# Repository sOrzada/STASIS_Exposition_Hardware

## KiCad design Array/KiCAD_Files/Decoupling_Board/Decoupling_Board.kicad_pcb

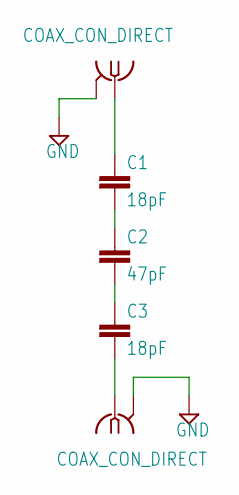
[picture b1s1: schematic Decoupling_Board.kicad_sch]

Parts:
C1, C3: 18pF; C1210
C2: 47pF; C1210
U$1, U$2: COAX_CON_DIRECT; COAX.141

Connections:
GND: U$1.P$2 (GND@1), U$2.P$2 (GND@1)
unnamed: C1.1, U$1.P$1 (1)
unnamed: C1.2, C2.1
unnamed: C2.2, C3.1
unnamed: C3.2, U$2.P$1 (1)

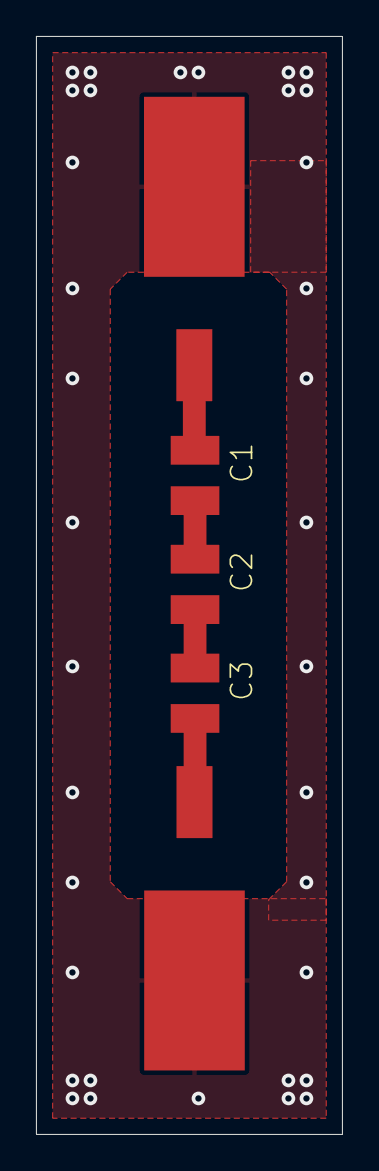
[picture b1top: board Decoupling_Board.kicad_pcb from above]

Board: 2 copper layers, 17.0 x 61.0 mm, 5 parts (0 on the bottom side), 5 nets.

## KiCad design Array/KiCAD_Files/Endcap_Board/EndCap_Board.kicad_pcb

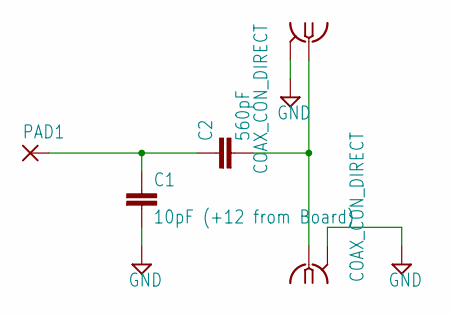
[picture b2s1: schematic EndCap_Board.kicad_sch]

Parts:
C1: 10pF (+12 from Board); C1210
C2: 560pF; C1210
PAD1: SMD5; SMD2,54-5,08
U$1, U$2: COAX_CON_DIRECT; COAX.141

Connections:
GND: C1.2, U$1.P$2 (GND@1), U$2.P$2 (GND@1)
unnamed: C1.1, C2.1, PAD1.1
unnamed: C2.2, U$1.P$1 (1), U$2.P$1 (1)

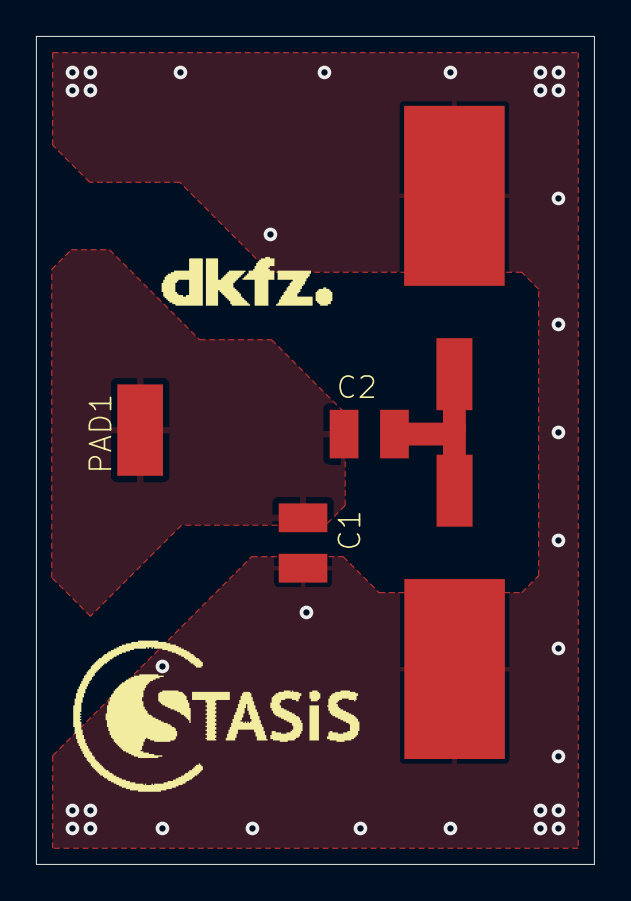
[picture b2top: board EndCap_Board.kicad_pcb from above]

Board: 2 copper layers, 31.0 x 46.0 mm, 7 parts (0 on the bottom side), 3 nets.

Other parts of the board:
U$3: LOGO_STASIS
U$4: LOGO_DKFZ

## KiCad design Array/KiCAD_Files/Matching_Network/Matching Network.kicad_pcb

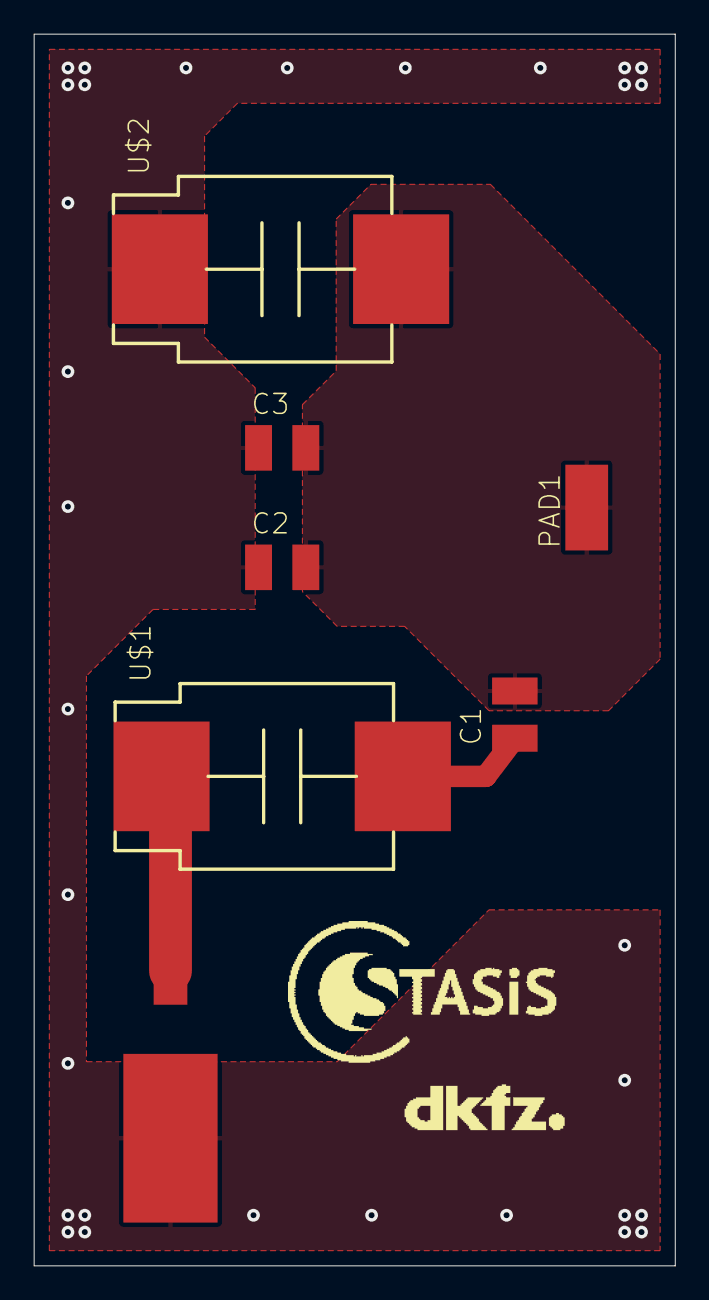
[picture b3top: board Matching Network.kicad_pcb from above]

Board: 2 copper layers, 38.0 x 73.0 mm, 9 parts (0 on the bottom side), 4 nets.

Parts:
C1, C2: 18pF; C1210_334
C3: 47pF; C1210_334
PAD1: SMD2,54-5,08_412
U$1, U$2: AJ25HV
U$3: COAX_CON_DIRECT; COAX.141
U$4: LOGO_STASIS
U$5: LOGO_DKFZ

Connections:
GND: C2.1, C3.1, U$2.P$1, U$3.P$2
unnamed: C1.1, U$1.P$2
unnamed: C1.2, C2.2, C3.2, PAD1.1, U$2.P$2
unnamed: U$1.P$1, U$3.P$1

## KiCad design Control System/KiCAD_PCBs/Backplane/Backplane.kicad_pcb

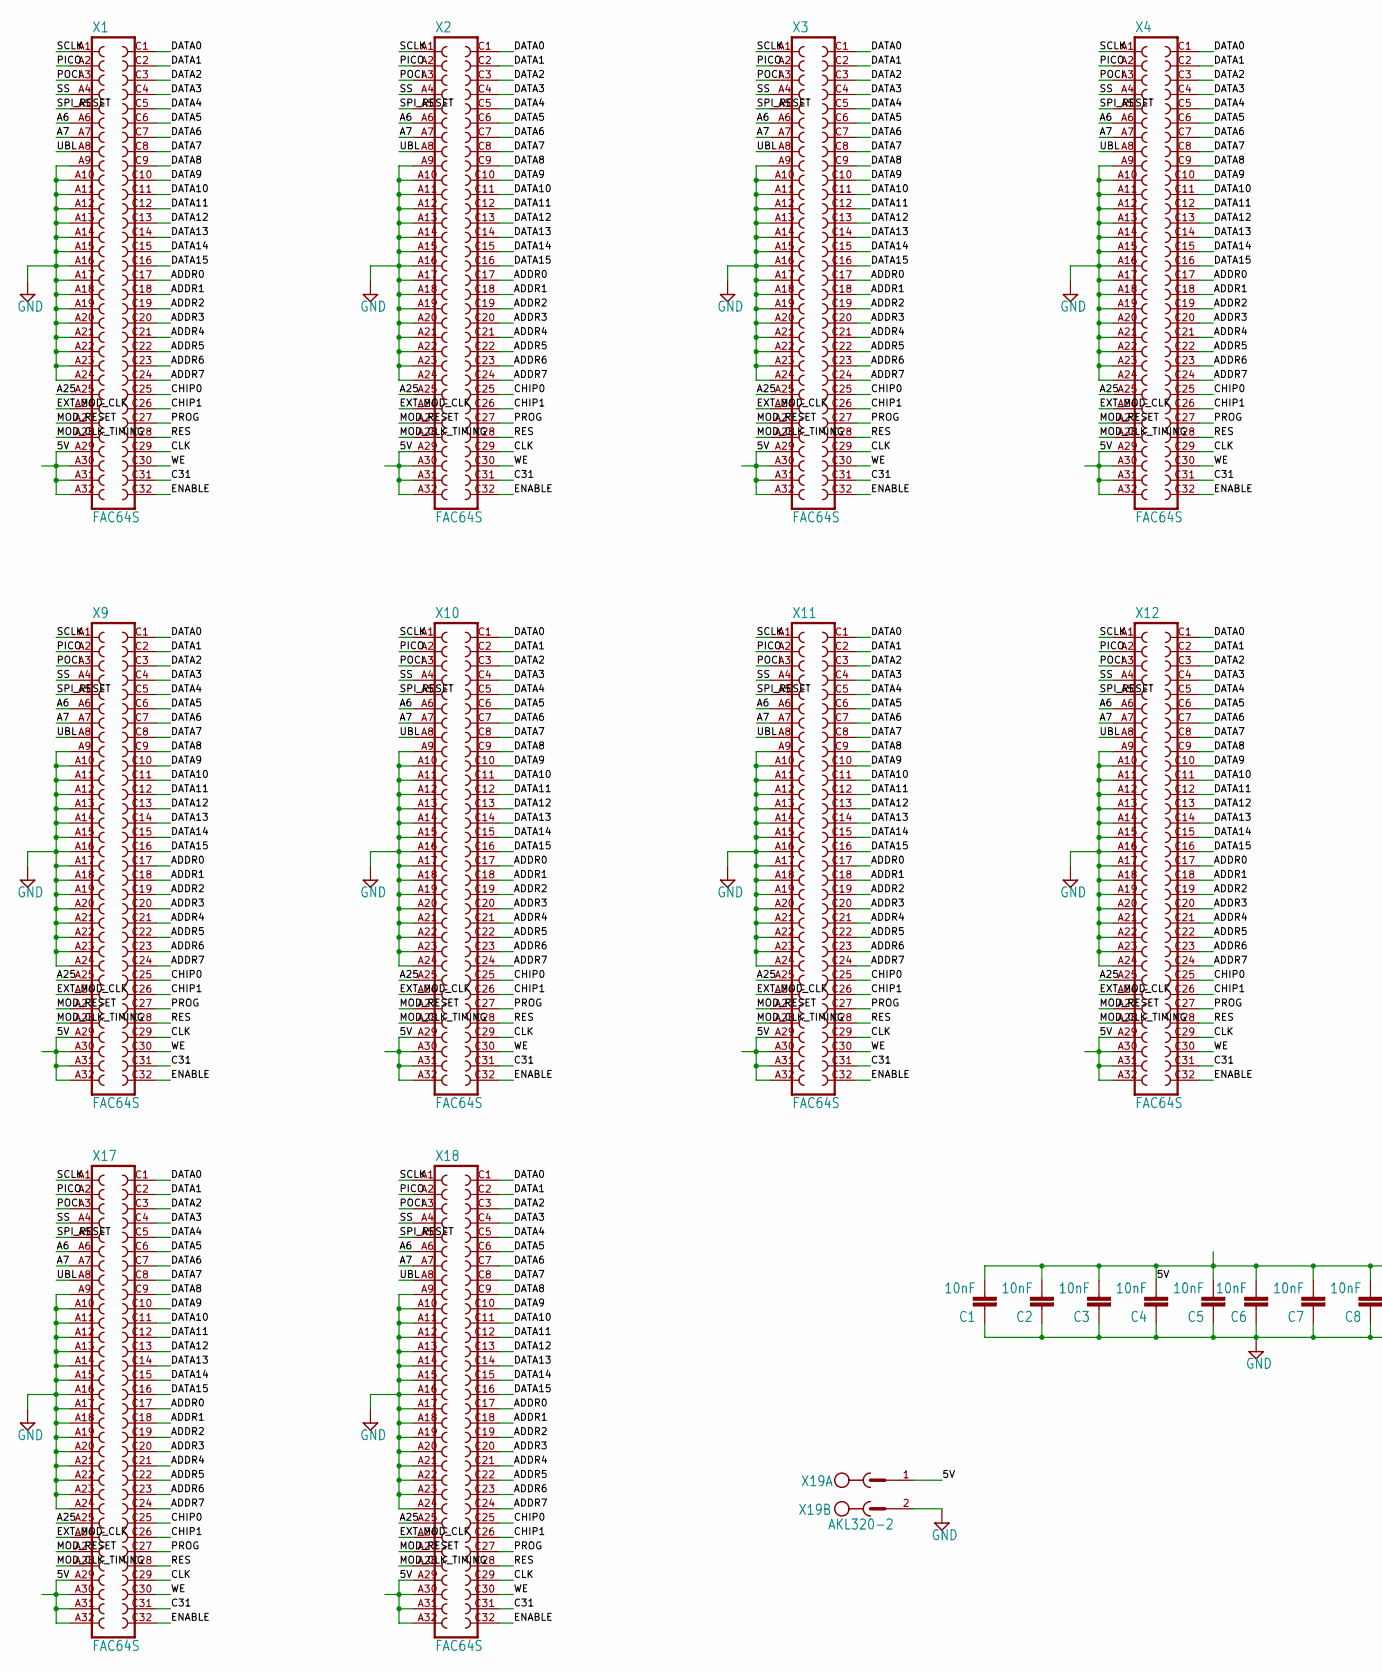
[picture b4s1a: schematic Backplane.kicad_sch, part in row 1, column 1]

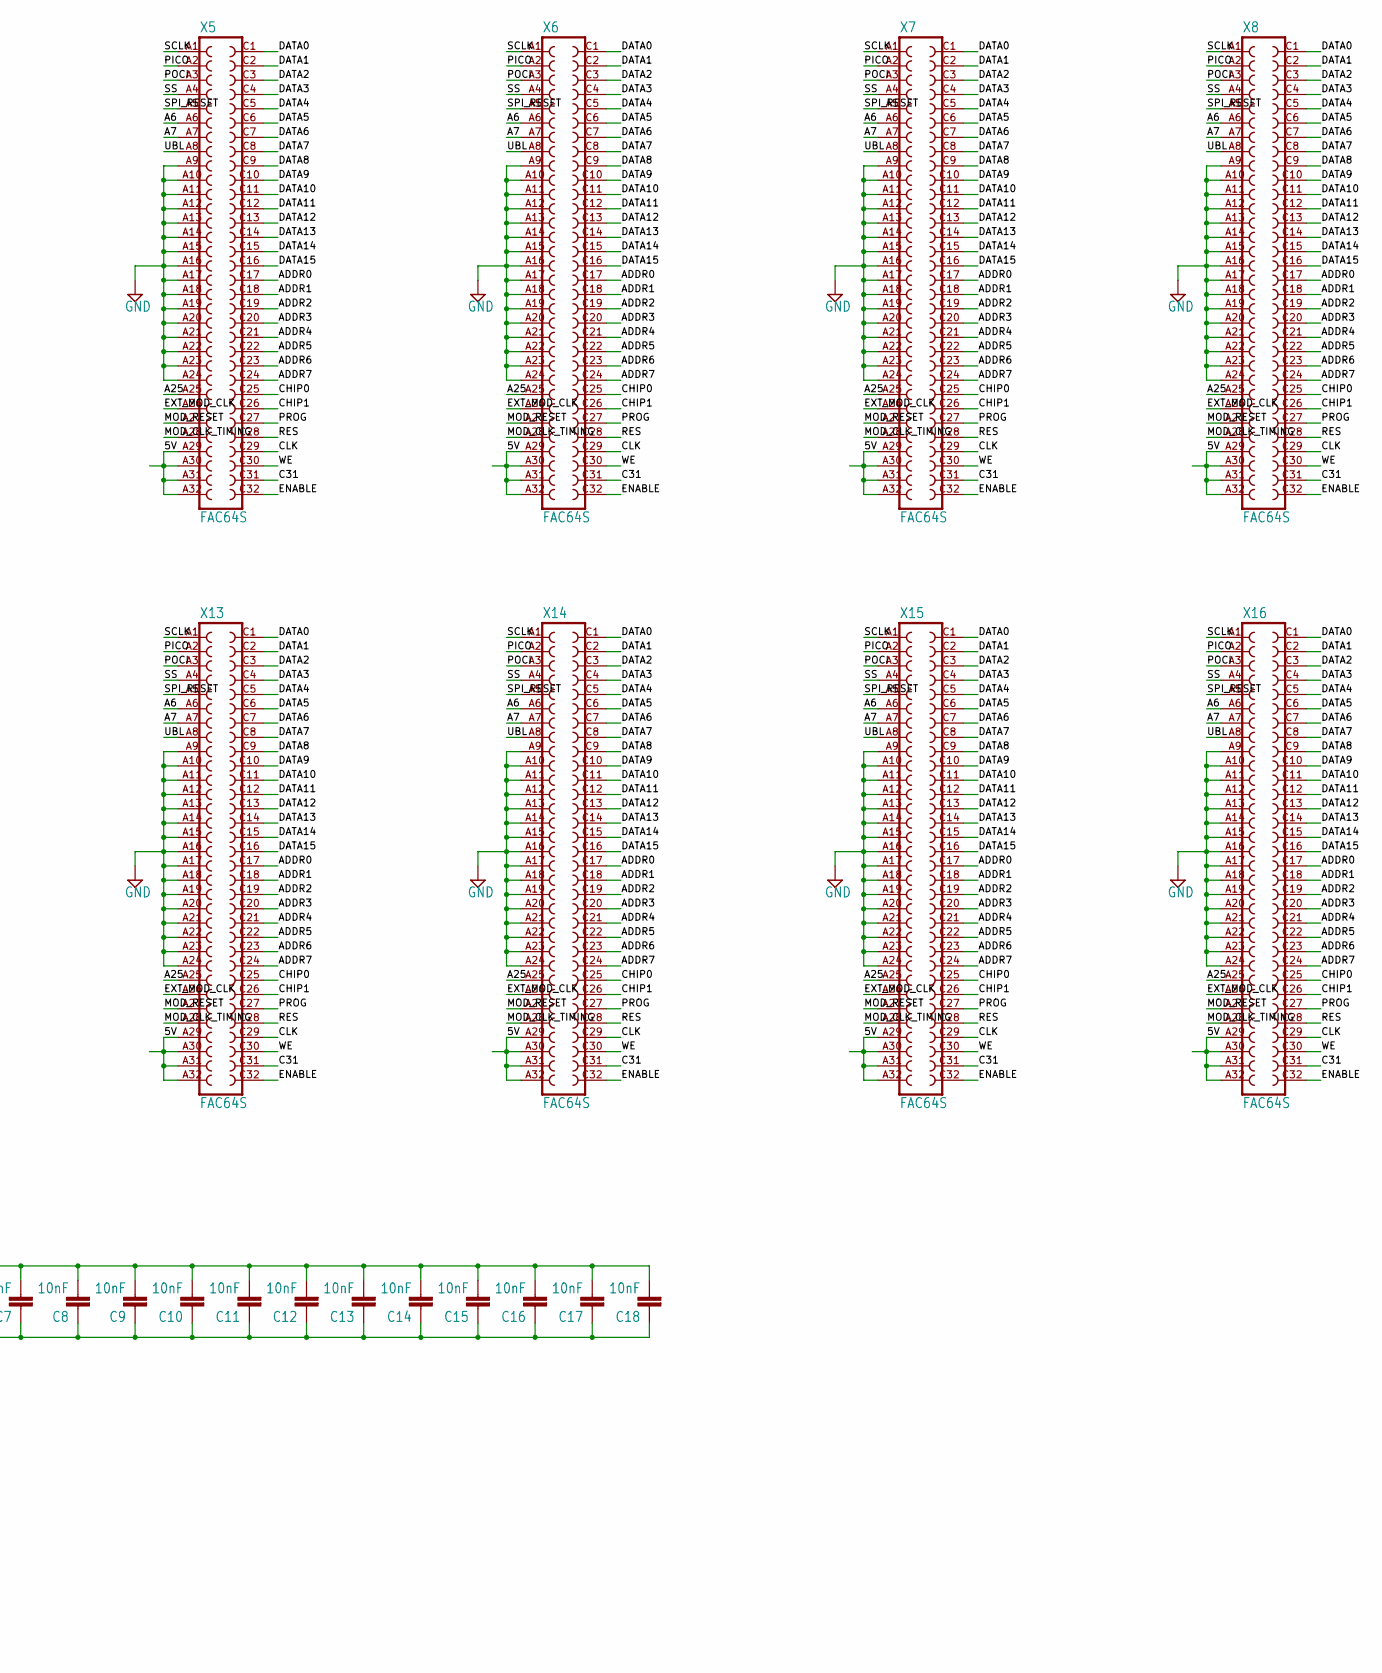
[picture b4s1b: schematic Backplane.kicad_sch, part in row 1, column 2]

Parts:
C1, C2, C3, C4, C5, C6, C7, C8, C9, C10, C11, C12, C13, C14, C15, C16, C17, C18: 10nF; C0603
X1, X2, X3, X4, X5, X6, X7, X8, X9, X10, X11, X12, X13, X14, X15, X16, X17, X18: FAC64S
X19: AKL320-2; MSTBV2

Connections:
5V: C1.2, C2.2, C3.2, C4.2, C5.2, C6.2, C7.2, C8.2, C9.2, C10.2, C11.2, C12.2, C13.2, C14.2, C15.2, C16.2, C17.2, C18.2, X1.A29, X1.A30, X1.A31, X1.A32, X2.A29, X2.A30, X2.A31, X2.A32, X3.A29, X3.A30, X3.A31, X3.A32, X4.A29, X4.A30, X4.A31, X4.A32, X5.A29, X5.A30, X5.A31, X5.A32, X6.A29, X6.A30, X6.A31, X6.A32, X7.A29, X7.A30, X7.A31, X7.A32, X8.A29, X8.A30, X8.A31, X8.A32, X9.A29, X9.A30, X9.A31, X9.A32, X10.A29, X10.A30, X10.A31, X10.A32, X11.A29, X11.A30, X11.A31, X11.A32, X12.A29, X12.A30, X12.A31, X12.A32, X13.A29, X13.A30, X13.A31, X13.A32, X14.A29, X14.A30, X14.A31, X14.A32, X15.A29, X15.A30, X15.A31, X15.A32, X16.A29, X16.A30, X16.A31, X16.A32, X17.A29, X17.A30, X17.A31, X17.A32, X18.A29, X18.A30, X18.A31, X18.A32, X19.1
A6: X1.A6, X2.A6, X3.A6, X4.A6, X5.A6, X6.A6, X7.A6, X8.A6, X9.A6, X10.A6, X11.A6, X12.A6, X13.A6, X14.A6, X15.A6, X16.A6, X17.A6, X18.A6
A7: X1.A7, X2.A7, X3.A7, X4.A7, X5.A7, X6.A7, X7.A7, X8.A7, X9.A7, X10.A7, X11.A7, X12.A7, X13.A7, X14.A7, X15.A7, X16.A7, X17.A7, X18.A7
A25: X1.A25, X2.A25, X3.A25, X4.A25, X5.A25, X6.A25, X7.A25, X8.A25, X9.A25, X10.A25, X11.A25, X12.A25, X13.A25, X14.A25, X15.A25, X16.A25, X17.A25, X18.A25
ADDR0: X1.C17, X2.C17, X3.C17, X4.C17, X5.C17, X6.C17, X7.C17, X8.C17, X9.C17, X10.C17, X11.C17, X12.C17, X13.C17, X14.C17, X15.C17, X16.C17, X17.C17, X18.C17
ADDR1: X1.C18, X2.C18, X3.C18, X4.C18, X5.C18, X6.C18, X7.C18, X8.C18, X9.C18, X10.C18, X11.C18, X12.C18, X13.C18, X14.C18, X15.C18, X16.C18, X17.C18, X18.C18
ADDR2: X1.C19, X2.C19, X3.C19, X4.C19, X5.C19, X6.C19, X7.C19, X8.C19, X9.C19, X10.C19, X11.C19, X12.C19, X13.C19, X14.C19, X15.C19, X16.C19, X17.C19, X18.C19
ADDR3: X1.C20, X2.C20, X3.C20, X4.C20, X5.C20, X6.C20, X7.C20, X8.C20, X9.C20, X10.C20, X11.C20, X12.C20, X13.C20, X14.C20, X15.C20, X16.C20, X17.C20, X18.C20
ADDR4: X1.C21, X2.C21, X3.C21, X4.C21, X5.C21, X6.C21, X7.C21, X8.C21, X9.C21, X10.C21, X11.C21, X12.C21, X13.C21, X14.C21, X15.C21, X16.C21, X17.C21, X18.C21
ADDR5: X1.C22, X2.C22, X3.C22, X4.C22, X5.C22, X6.C22, X7.C22, X8.C22, X9.C22, X10.C22, X11.C22, X12.C22, X13.C22, X14.C22, X15.C22, X16.C22, X17.C22, X18.C22
ADDR6: X1.C23, X2.C23, X3.C23, X4.C23, X5.C23, X6.C23, X7.C23, X8.C23, X9.C23, X10.C23, X11.C23, X12.C23, X13.C23, X14.C23, X15.C23, X16.C23, X17.C23, X18.C23
ADDR7: X1.C24, X2.C24, X3.C24, X4.C24, X5.C24, X6.C24, X7.C24, X8.C24, X9.C24, X10.C24, X11.C24, X12.C24, X13.C24, X14.C24, X15.C24, X16.C24, X17.C24, X18.C24
C31: X1.C31, X2.C31, X3.C31, X4.C31, X5.C31, X6.C31, X7.C31, X8.C31, X9.C31, X10.C31, X11.C31, X12.C31, X13.C31, X14.C31, X15.C31, X16.C31, X17.C31, X18.C31
CHIP0: X1.C25, X2.C25, X3.C25, X4.C25, X5.C25, X6.C25, X7.C25, X8.C25, X9.C25, X10.C25, X11.C25, X12.C25, X13.C25, X14.C25, X15.C25, X16.C25, X17.C25, X18.C25
CHIP1: X1.C26, X2.C26, X3.C26, X4.C26, X5.C26, X6.C26, X7.C26, X8.C26, X9.C26, X10.C26, X11.C26, X12.C26, X13.C26, X14.C26, X15.C26, X16.C26, X17.C26, X18.C26
CLK: X1.C29, X2.C29, X3.C29, X4.C29, X5.C29, X6.C29, X7.C29, X8.C29, X9.C29, X10.C29, X11.C29, X12.C29, X13.C29, X14.C29, X15.C29, X16.C29, X17.C29, X18.C29
DATA0: X1.C1, X2.C1, X3.C1, X4.C1, X5.C1, X6.C1, X7.C1, X8.C1, X9.C1, X10.C1, X11.C1, X12.C1, X13.C1, X14.C1, X15.C1, X16.C1, X17.C1, X18.C1
DATA1: X1.C2, X2.C2, X3.C2, X4.C2, X5.C2, X6.C2, X7.C2, X8.C2, X9.C2, X10.C2, X11.C2, X12.C2, X13.C2, X14.C2, X15.C2, X16.C2, X17.C2, X18.C2
DATA2: X1.C3, X2.C3, X3.C3, X4.C3, X5.C3, X6.C3, X7.C3, X8.C3, X9.C3, X10.C3, X11.C3, X12.C3, X13.C3, X14.C3, X15.C3, X16.C3, X17.C3, X18.C3
DATA3: X1.C4, X2.C4, X3.C4, X4.C4, X5.C4, X6.C4, X7.C4, X8.C4, X9.C4, X10.C4, X11.C4, X12.C4, X13.C4, X14.C4, X15.C4, X16.C4, X17.C4, X18.C4
DATA4: X1.C5, X2.C5, X3.C5, X4.C5, X5.C5, X6.C5, X7.C5, X8.C5, X9.C5, X10.C5, X11.C5, X12.C5, X13.C5, X14.C5, X15.C5, X16.C5, X17.C5, X18.C5
DATA5: X1.C6, X2.C6, X3.C6, X4.C6, X5.C6, X6.C6, X7.C6, X8.C6, X9.C6, X10.C6, X11.C6, X12.C6, X13.C6, X14.C6, X15.C6, X16.C6, X17.C6, X18.C6
DATA6: X1.C7, X2.C7, X3.C7, X4.C7, X5.C7, X6.C7, X7.C7, X8.C7, X9.C7, X10.C7, X11.C7, X12.C7, X13.C7, X14.C7, X15.C7, X16.C7, X17.C7, X18.C7
DATA7: X1.C8, X2.C8, X3.C8, X4.C8, X5.C8, X6.C8, X7.C8, X8.C8, X9.C8, X10.C8, X11.C8, X12.C8, X13.C8, X14.C8, X15.C8, X16.C8, X17.C8, X18.C8
DATA8: X1.C9, X2.C9, X3.C9, X4.C9, X5.C9, X6.C9, X7.C9, X8.C9, X9.C9, X10.C9, X11.C9, X12.C9, X13.C9, X14.C9, X15.C9, X16.C9, X17.C9, X18.C9
DATA9: X1.C10, X2.C10, X3.C10, X4.C10, X5.C10, X6.C10, X7.C10, X8.C10, X9.C10, X10.C10, X11.C10, X12.C10, X13.C10, X14.C10, X15.C10, X16.C10, X17.C10, X18.C10
DATA10: X1.C11, X2.C11, X3.C11, X4.C11, X5.C11, X6.C11, X7.C11, X8.C11, X9.C11, X10.C11, X11.C11, X12.C11, X13.C11, X14.C11, X15.C11, X16.C11, X17.C11, X18.C11
DATA11: X1.C12, X2.C12, X3.C12, X4.C12, X5.C12, X6.C12, X7.C12, X8.C12, X9.C12, X10.C12, X11.C12, X12.C12, X13.C12, X14.C12, X15.C12, X16.C12, X17.C12, X18.C12
DATA12: X1.C13, X2.C13, X3.C13, X4.C13, X5.C13, X6.C13, X7.C13, X8.C13, X9.C13, X10.C13, X11.C13, X12.C13, X13.C13, X14.C13, X15.C13, X16.C13, X17.C13, X18.C13
DATA13: X1.C14, X2.C14, X3.C14, X4.C14, X5.C14, X6.C14, X7.C14, X8.C14, X9.C14, X10.C14, X11.C14, X12.C14, X13.C14, X14.C14, X15.C14, X16.C14, X17.C14, X18.C14
DATA14: X1.C15, X2.C15, X3.C15, X4.C15, X5.C15, X6.C15, X7.C15, X8.C15, X9.C15, X10.C15, X11.C15, X12.C15, X13.C15, X14.C15, X15.C15, X16.C15, X17.C15, X18.C15
DATA15: X1.C16, X2.C16, X3.C16, X4.C16, X5.C16, X6.C16, X7.C16, X8.C16, X9.C16, X10.C16, X11.C16, X12.C16, X13.C16, X14.C16, X15.C16, X16.C16, X17.C16, X18.C16
ENABLE: X1.C32, X2.C32, X3.C32, X4.C32, X5.C32, X6.C32, X7.C32, X8.C32, X9.C32, X10.C32, X11.C32, X12.C32, X13.C32, X14.C32, X15.C32, X16.C32, X17.C32, X18.C32
EXT_MOD_CLK: X1.A26, X2.A26, X3.A26, X4.A26, X5.A26, X6.A26, X7.A26, X8.A26, X9.A26, X10.A26, X11.A26, X12.A26, X13.A26, X14.A26, X15.A26, X16.A26, X17.A26, X18.A26
GND: C1.1, C2.1, C3.1, C4.1, C5.1, C6.1, C7.1, C8.1, C9.1, C10.1, C11.1, C12.1, C13.1, C14.1, C15.1, C16.1, C17.1, C18.1, X1.A9, X1.A10, X1.A11, X1.A12, X1.A13, X1.A14, X1.A15, X1.A16, X1.A17, X1.A18, X1.A19, X1.A20, X1.A21, X1.A22, X1.A23, X1.A24, X2.A9, X2.A10, X2.A11, X2.A12, X2.A13, X2.A14, X2.A15, X2.A16, X2.A17, X2.A18, X2.A19, X2.A20, X2.A21, X2.A22, X2.A23, X2.A24, X3.A9, X3.A10, X3.A11, X3.A12, X3.A13, X3.A14, X3.A15, X3.A16, X3.A17, X3.A18, X3.A19, X3.A20, X3.A21, X3.A22, X3.A23, X3.A24, X4.A9, X4.A10, X4.A11, X4.A12, X4.A13, X4.A14, X4.A15, X4.A16, X4.A17, X4.A18, X4.A19, X4.A20, X4.A21, X4.A22, X4.A23, X4.A24, X5.A9, X5.A10, X5.A11, X5.A12, X5.A13, X5.A14, X5.A15, X5.A16, X5.A17, X5.A18, X5.A19, X5.A20, X5.A21, X5.A22, X5.A23, X5.A24, X6.A9, X6.A10, X6.A11, X6.A12, X6.A13, X6.A14, X6.A15, X6.A16, X6.A17, X6.A18, X6.A19, X6.A20, X6.A21, X6.A22, X6.A23, X6.A24, X7.A9, X7.A10, X7.A11, X7.A12, X7.A13, X7.A14, X7.A15, X7.A16, X7.A17, X7.A18, X7.A19, X7.A20, X7.A21, X7.A22, X7.A23, X7.A24, X8.A9, X8.A10, X8.A11, X8.A12, X8.A13, X8.A14, X8.A15, X8.A16, X8.A17, X8.A18, X8.A19, X8.A20, X8.A21, X8.A22, X8.A23, X8.A24, X9.A9, X9.A10, X9.A11, X9.A12, X9.A13, X9.A14, X9.A15, X9.A16, X9.A17, X9.A18, X9.A19, X9.A20, X9.A21, X9.A22, X9.A23, X9.A24, X10.A9, X10.A10, X10.A11, X10.A12, X10.A13, X10.A14, X10.A15, X10.A16, X10.A17, X10.A18, X10.A19, X10.A20, X10.A21, X10.A22, X10.A23, X10.A24, X11.A9, X11.A10, X11.A11, X11.A12, X11.A13, X11.A14, X11.A15, X11.A16, X11.A17, X11.A18, X11.A19, X11.A20, X11.A21, X11.A22, X11.A23, X11.A24, X12.A9, X12.A10, X12.A11, X12.A12, X12.A13, X12.A14, X12.A15, X12.A16, X12.A17, X12.A18, X12.A19, X12.A20, X12.A21, X12.A22, X12.A23, X12.A24, X13.A9, X13.A10, X13.A11, X13.A12, X13.A13, X13.A14, X13.A15, X13.A16, X13.A17, X13.A18, X13.A19, X13.A20, X13.A21, X13.A22, X13.A23, X13.A24, X14.A9, X14.A10, X14.A11, X14.A12, X14.A13, X14.A14, X14.A15, X14.A16, X14.A17, X14.A18, X14.A19, X14.A20, X14.A21, X14.A22, X14.A23, X14.A24, X15.A9, X15.A10, X15.A11, X15.A12, X15.A13, X15.A14, X15.A15, X15.A16, X15.A17, X15.A18, X15.A19, X15.A20, X15.A21, X15.A22, X15.A23, X15.A24, X16.A9, X16.A10, X16.A11, X16.A12, X16.A13, X16.A14, X16.A15, X16.A16, X16.A17, X16.A18, X16.A19, X16.A20, X16.A21, X16.A22, X16.A23, X16.A24, X17.A9, X17.A10, X17.A11, X17.A12, X17.A13, X17.A14, X17.A15, X17.A16, X17.A17, X17.A18, X17.A19, X17.A20, X17.A21, X17.A22, X17.A23, X17.A24, X18.A9, X18.A10, X18.A11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
MOD_CLK_TIMING: X1.A28, X2.A28, X3.A28, X4.A28, X5.A28, X6.A28, X7.A28, X8.A28, X9.A28, X10.A28, X11.A28, X12.A28, X13.A28, X14.A28, X15.A28, X16.A28, X17.A28, X18.A28
MOD_RESET: X1.A27, X2.A27, X3.A27, X4.A27, X5.A27, X6.A27, X7.A27, X8.A27, X9.A27, X10.A27, X11.A27, X12.A27, X13.A27, X14.A27, X15.A27, X16.A27, X17.A27, X18.A27
PICO: X1.A2, X2.A2, X3.A2, X4.A2, X5.A2, X6.A2, X7.A2, X8.A2, X9.A2, X10.A2, X11.A2, X12.A2, X13.A2, X14.A2, X15.A2, X16.A2, X17.A2, X18.A2
POCI: X1.A3, X2.A3, X3.A3, X4.A3, X5.A3, X6.A3, X7.A3, X8.A3, X9.A3, X10.A3, X11.A3, X12.A3, X13.A3, X14.A3, X15.A3, X16.A3, X17.A3, X18.A3
PROG: X1.C27, X2.C27, X3.C27, X4.C27, X5.C27, X6.C27, X7.C27, X8.C27, X9.C27, X10.C27, X11.C27, X12.C27, X13.C27, X14.C27, X15.C27, X16.C27, X17.C27, X18.C27
RES: X1.C28, X2.C28, X3.C28, X4.C28, X5.C28, X6.C28, X7.C28, X8.C28, X9.C28, X10.C28, X11.C28, X12.C28, X13.C28, X14.C28, X15.C28, X16.C28, X17.C28, X18.C28
SCLK: X1.A1, X2.A1, X3.A1, X4.A1, X5.A1, X6.A1, X7.A1, X8.A1, X9.A1, X10.A1, X11.A1, X12.A1, X13.A1, X14.A1, X15.A1, X16.A1, X17.A1, X18.A1
SPI_RESET: X1.A5, X2.A5, X3.A5, X4.A5, X5.A5, X6.A5, X7.A5, X8.A5, X9.A5, X10.A5, X11.A5, X12.A5, X13.A5, X14.A5, X15.A5, X16.A5, X17.A5, X18.A5
SS: X1.A4, X2.A4, X3.A4, X4.A4, X5.A4, X6.A4, X7.A4, X8.A4, X9.A4, X10.A4, X11.A4, X12.A4, X13.A4, X14.A4, X15.A4, X16.A4, X17.A4, X18.A4
UBL: X1.A8, X2.A8, X3.A8, X4.A8, X5.A8, X6.A8, X7.A8, X8.A8, X9.A8, X10.A8, X11.A8, X12.A8, X13.A8, X14.A8, X15.A8, X16.A8, X17.A8, X18.A8
WE: X1.C30, X2.C30, X3.C30, X4.C30, X5.C30, X6.C30, X7.C30, X8.C30, X9.C30, X10.C30, X11.C30, X12.C30, X13.C30, X14.C30, X15.C30, X16.C30, X17.C30, X18.C30

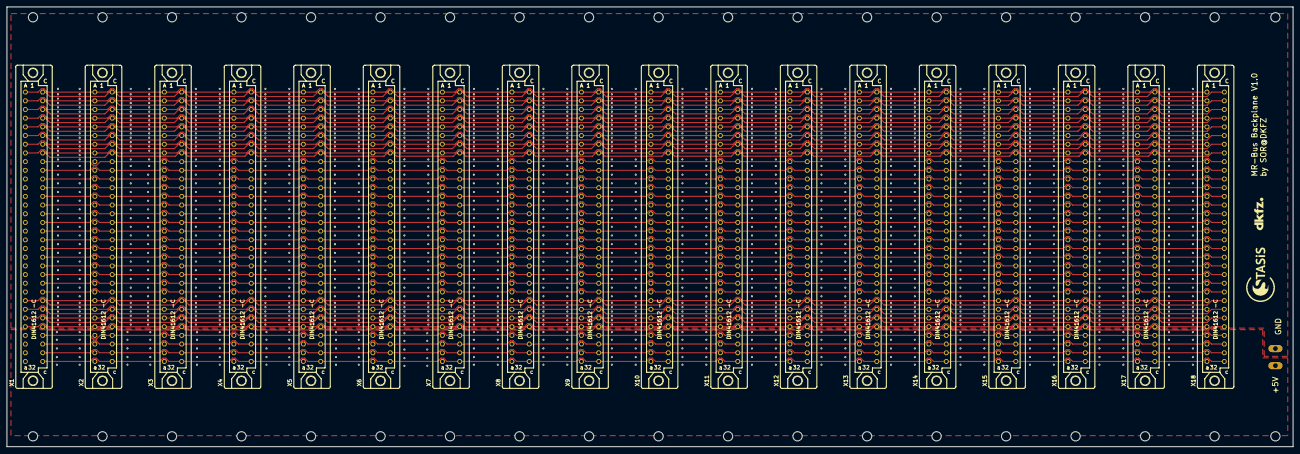
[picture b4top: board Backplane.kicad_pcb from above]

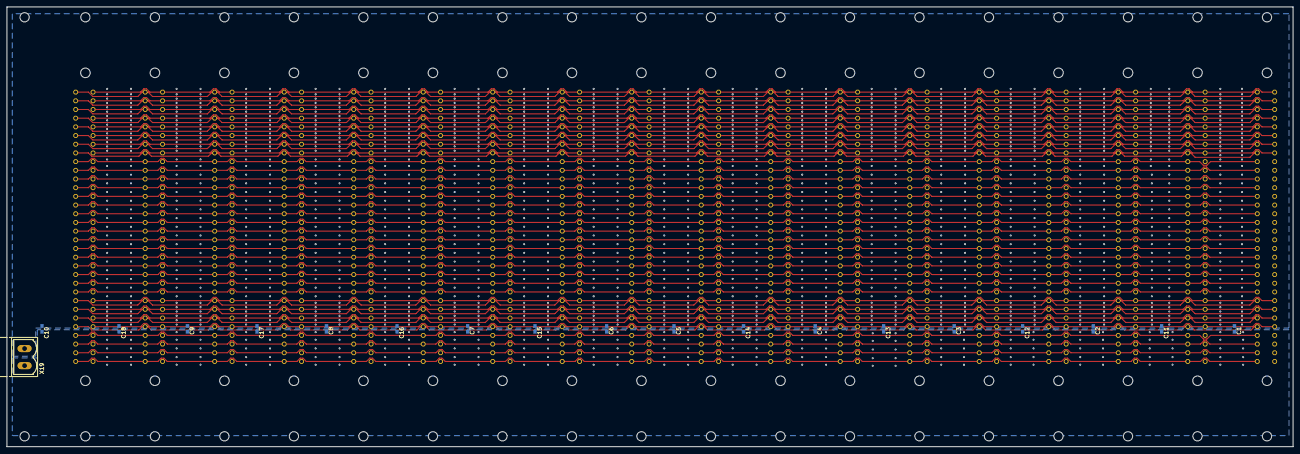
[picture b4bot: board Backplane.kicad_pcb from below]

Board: 2 copper layers, 376.0 x 128.6 mm, 77 parts (19 on the bottom side), 46 nets.

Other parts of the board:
@HOLE0, @HOLE1, @HOLE2, @HOLE3, @HOLE4, @HOLE5, @HOLE6, @HOLE7, @HOLE8, @HOLE9, @HOLE10, @HOLE11, @HOLE12, @HOLE13, @HOLE14, @HOLE15, @HOLE16, @HOLE17, @HOLE18, @HOLE19, @HOLE20, @HOLE21, @HOLE22, @HOLE23, @HOLE24, @HOLE25, @HOLE26, @HOLE27, @HOLE28, @HOLE29, @HOLE30, @HOLE31, @HOLE32, @HOLE33, @HOLE34, @HOLE35, @HOLE36, @HOLE37: (no value)
U$1: LOGO_STASIS
U$2: LOGO_DKFZ

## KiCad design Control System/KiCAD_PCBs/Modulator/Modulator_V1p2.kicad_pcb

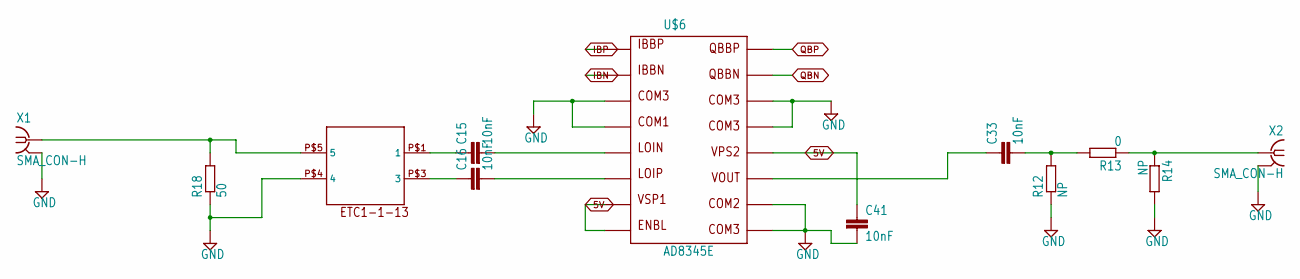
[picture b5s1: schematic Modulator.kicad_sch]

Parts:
C15, C16, C33: 10nF; C0402
C41: 10nF; C0603
R12, R14: NP; R0805
R13: 0; R0805
R18: 50; R0603
U$6: AD8345E; TSSOP16EXP
U$12: ETC1-1-13
X1, X2: SMA_CON-H; BU-SMA-H

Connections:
5V: C41.1, U$6.7, U$6.8, U$6.12; also elsewhere on the board
GND: C41.2, R12.1, R14.2, R18.1, U$6.3, U$6.4, U$6.9, U$6.10, U$6.13, U$6.14, U$6.EXP, U$12.P$4 (4), X1.2 (GND@1), X1.3 (GND@1), X1.4 (GND@1), X1.5 (GND@1), X2.2 (GND@1), X2.3 (GND@1), X2.4 (GND@1), X2.5 (GND@1); also elsewhere on the board
IBN: U$6.2; also elsewhere on the board
IBP: U$6.1; also elsewhere on the board
unnamed: C33.1, U$6.11
unnamed: C15.1, U$12.P$1 (1)
unnamed: C16.1, U$12.P$3 (3)
unnamed: R18.2, U$12.P$5 (5), X1.1
unnamed: C15.2, U$6.5
unnamed: C16.2, U$6.6
unnamed: R13.1, R14.1, X2.1
unnamed: C33.2, R12.2, R13.2
QBN: U$6.15; also elsewhere on the board
QBP: U$6.16; also elsewhere on the board

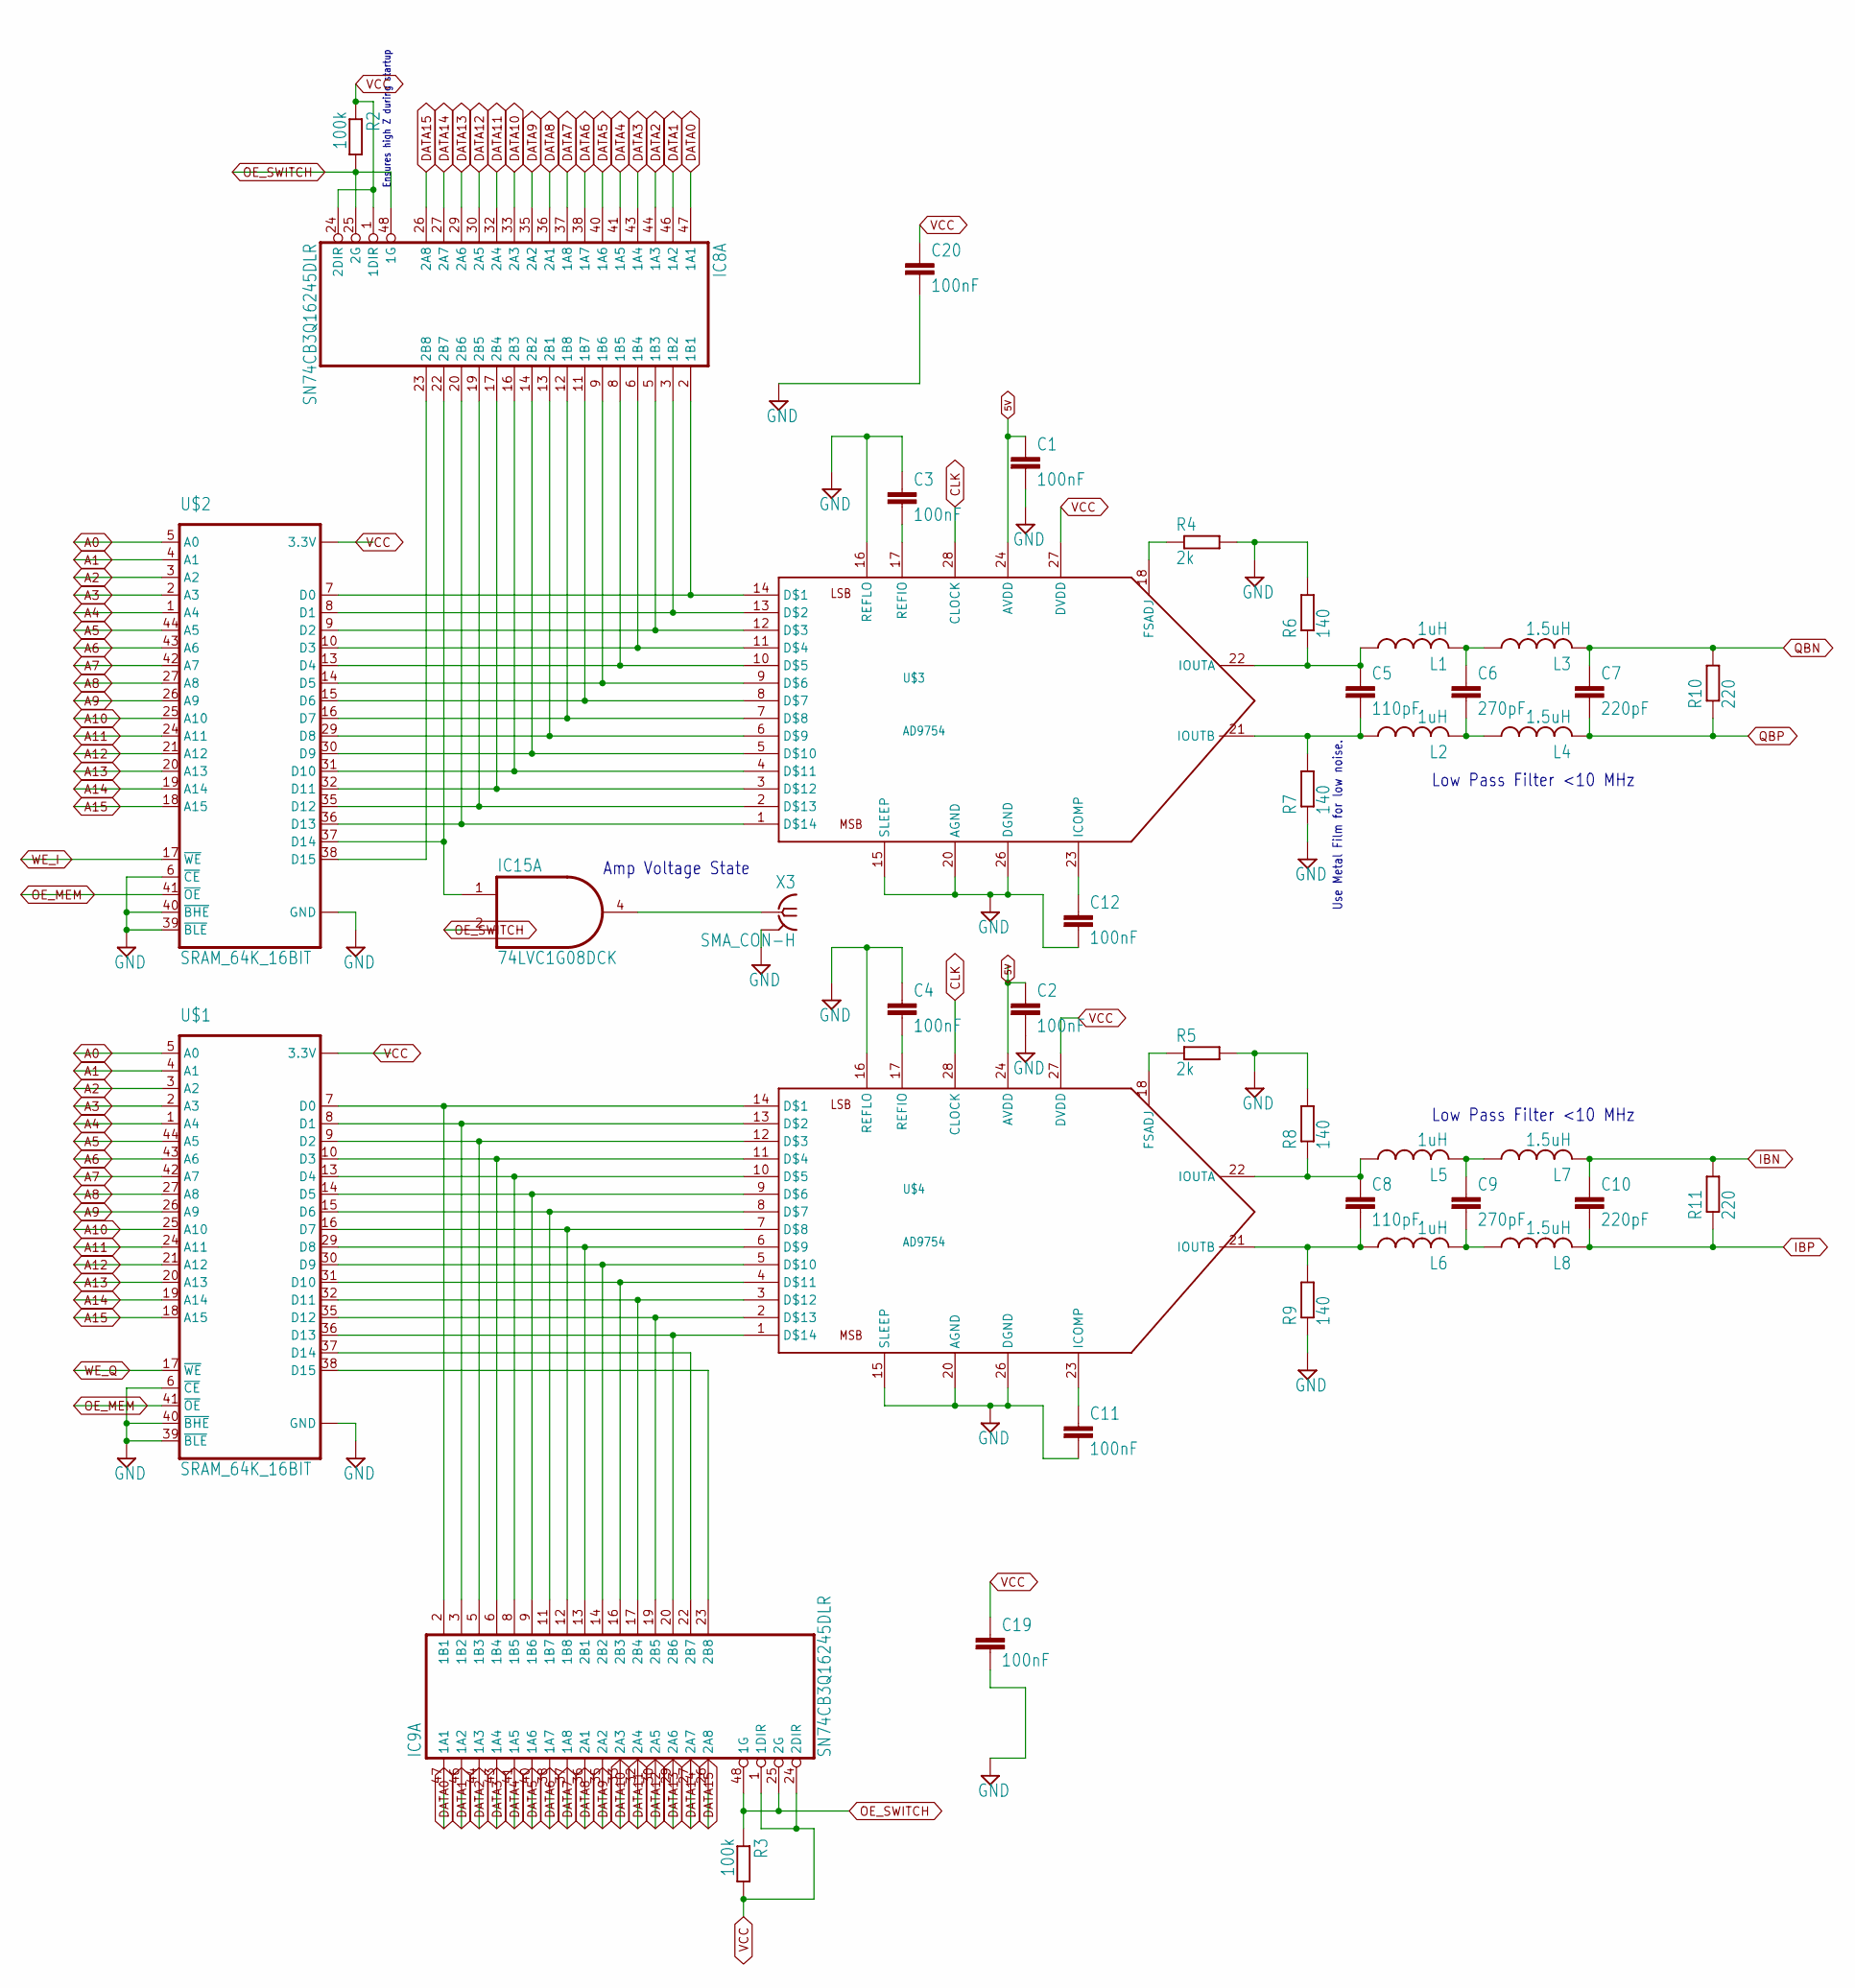
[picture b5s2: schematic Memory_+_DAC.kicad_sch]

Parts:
C1, C2, C3, C4, C11, C12, C19, C20: 100nF; C0603
C5, C8: 110pF; C0603
C6, C9: 270pF; C0603
C7, C10: 220pF; C0603
IC8, IC9: SN74CB3Q16245DLR; SSOP48DL
IC15: 74LVC1G08DCK; SC70-5
L1, L2, L5, L6: 1uH; L2012C
L3, L4, L7, L8: 1.5uH; L2012C
R2, R3: 100k; R0603
R4, R5: 2k; R0603
R6, R7, R8, R9: 140; R0603
R10, R11: 220; R0603
U$1, U$2: SRAM_64K_16BIT; TSOPII-Z44
U$3, U$4: AD9754; TSSOP28
X3: SMA_CON-H; BU-SMA-H

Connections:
5V: C1.1, C2.1, U$3.24 (AVDD), U$4.24 (AVDD); also elsewhere on the board
A0: U$1.5 (A0), U$2.5 (A0); also elsewhere on the board
A1: U$1.4 (A1), U$2.4 (A1); also elsewhere on the board
A2: U$1.3 (A2), U$2.3 (A2); also elsewhere on the board
A3: U$1.2 (A3), U$2.2 (A3); also elsewhere on the board
A4: U$1.1 (A4), U$2.1 (A4); also elsewhere on the board
A5: U$1.44 (A5), U$2.44 (A5); also elsewhere on the board
A6: U$1.43 (A6), U$2.43 (A6); also elsewhere on the board
A7: U$1.42 (A7), U$2.42 (A7); also elsewhere on the board
A8: U$1.27 (A8), U$2.27 (A8); also elsewhere on the board
A9: U$1.26 (A9), U$2.26 (A9); also elsewhere on the board
A10: U$1.25 (A10), U$2.25 (A10); also elsewhere on the board
A11: U$1.24 (A11), U$2.24 (A11); also elsewhere on the board
A12: U$1.21 (A12), U$2.21 (A12); also elsewhere on the board
A13: U$1.20 (A13), U$2.20 (A13); also elsewhere on the board
A14: U$1.19 (A14), U$2.19 (A14); also elsewhere on the board
A15: U$1.18 (A15), U$2.18 (A15); also elsewhere on the board
CLK: U$3.28 (CLOCK), U$4.28 (CLOCK); also elsewhere on the board
DATA0: IC8.47 (1A1), IC9.47 (1A1); also elsewhere on the board
DATA1: IC8.46 (1A2), IC9.46 (1A2); also elsewhere on the board
DATA2: IC8.44 (1A3), IC9.44 (1A3); also elsewhere on the board
DATA3: IC8.43 (1A4), IC9.43 (1A4); also elsewhere on the board
DATA4: IC8.41 (1A5), IC9.41 (1A5); also elsewhere on the board
DATA5: IC8.40 (1A6), IC9.40 (1A6); also elsewhere on the board
DATA6: IC8.38 (1A7), IC9.38 (1A7); also elsewhere on the board
DATA7: IC8.37 (1A8), IC9.37 (1A8); also elsewhere on the board
DATA8: IC8.36 (2A1), IC9.36 (2A1); also elsewhere on the board
DATA9: IC8.35 (2A2), IC9.35 (2A2); also elsewhere on the board
DATA10: IC8.33 (2A3), IC9.33 (2A3); also elsewhere on the board
DATA11: IC8.32 (2A4), IC9.32 (2A4); also elsewhere on the board
DATA12: IC8.30 (2A5), IC9.30 (2A5); also elsewhere on the board
DATA13: IC8.29 (2A6), IC9.29 (2A6); also elsewhere on the board
DATA14: IC8.27 (2A7), IC9.27 (2A7); also elsewhere on the board
DATA15: IC8.26 (2A8), IC9.26 (2A8); also elsewhere on the board
DI0: IC8.2 (1B1), U$2.7 (D0), U$3.14
DI1: IC8.3 (1B2), U$2.8 (D1), U$3.13
DI2: IC8.5 (1B3), U$2.9 (D2), U$3.12
DI3: IC8.6 (1B4), U$2.10 (D3), U$3.11
DI4: IC8.8 (1B5), U$2.13 (D4), U$3.10
DI5: IC8.9 (1B6), U$2.14 (D5), U$3.9
DI6: IC8.11 (1B7), U$2.15 (D6), U$3.8
DI7: IC8.12 (1B8), U$2.16 (D7), U$3.7
DI8: IC8.13 (2B1), U$2.29 (D8), U$3.6
DI9: IC8.14 (2B2), U$2.30 (D9), U$3.5
DI10: IC8.16 (2B3), U$2.31 (D10), U$3.4
DI11: IC8.17 (2B4), U$2.32 (D11), U$3.3
DI12: IC8.19 (2B5), U$2.35 (D12), U$3.2
DI13: IC8.20 (2B6), U$2.36 (D13), U$3.1
DQ0: IC9.2 (1B1), U$1.7 (D0), U$4.14
DQ1: IC9.3 (1B2), U$1.8 (D1), U$4.13
DQ2: IC9.5 (1B3), U$1.9 (D2), U$4.12
DQ3: IC9.6 (1B4), U$1.10 (D3), U$4.11
DQ4: IC9.8 (1B5), U$1.13 (D4), U$4.10
DQ5: IC9.9 (1B6), U$1.14 (D5), U$4.9
DQ6: IC9.11 (1B7), U$1.15 (D6), U$4.8
DQ7: IC9.12 (1B8), U$1.16 (D7), U$4.7
DQ8: IC9.13 (2B1), U$1.29 (D8), U$4.6
DQ9: IC9.14 (2B2), U$1.30 (D9), U$4.5
DQ10: IC9.16 (2B3), U$1.31 (D10), U$4.4
DQ11: IC9.17 (2B4), U$1.32 (D11), U$4.3
DQ12: IC9.19 (2B5), U$1.35 (D12), U$4.2
DQ13: IC9.20 (2B6), U$1.36 (D13), U$4.1
GND: C1.2, C2.2, C3.1, C4.1, C11.2, C12.2, C19.2, C20.2, IC8.4 (GND@1), IC8.10 (GND@2), IC8.15 (GND@3), IC8.21 (GND@4), IC8.28 (GND@5), IC8.34 (GND@6), IC8.39 (GND@7), IC8.45 (GND@8), IC9.4 (GND@1), IC9.10 (GND@2), IC9.15 (GND@3), IC9.21 (GND@4), IC9.28 (GND@5), IC9.34 (GND@6), IC9.39 (GND@7), IC9.45 (GND@8), IC15.3 (GND), R4.2, R5.2, R6.2, R7.1, R8.2, R9.1, U$1.6 (~CE), U$1.12 (GND), U$1.34 (GND), U$1.39 (~BLE), U$1.40 (~BHE), U$2.6 (~CE), U$2.12 (GND), U$2.34 (GND), U$2.39 (~BLE), U$2.40 (~BHE), U$3.15 (SLEEP), U$3.16 (REFLO), U$3.20 (AGND), U$3.26 (DGND), U$4.15 (SLEEP), U$4.16 (REFLO), U$4.20 (AGND), U$4.26 (DGND), X3.2 (GND@1), X3.3 (GND@1), X3.4 (GND@1), X3.5 (GND@1); also elsewhere on the board
IBN: C10.1, L7.2, R11.2; also elsewhere on the board
IBP: C10.2, L8.2, R11.1; also elsewhere on the board
unnamed: IC8.22 (2B7), IC15.1 (I0), U$2.37 (D14)
unnamed: IC8.23 (2B8), U$2.38 (D15)
unnamed: IC9.22 (2B7), U$1.37 (D14)
unnamed: IC9.23 (2B8), U$1.38 (D15)
unnamed: R5.1, U$4.18 (FSADJ)
unnamed: IC15.4 (O), X3.1
unnamed: C6.1, L1.2, L3.1
unnamed: R4.1, U$3.18 (FSADJ)
unnamed: C6.2, L2.2, L4.1
unnamed: C3.2, U$3.17 (REFIO)
unnamed: C4.2, U$4.17 (REFIO)
unnamed: C8.1, L5.1, R8.1, U$4.22 (IOUTA)
unnamed: C8.2, L6.1, R9.2, U$4.21 (IOUTB)
unnamed: C5.1, L1.1, R6.1, U$3.22 (IOUTA)
unnamed: C9.1, L5.2, L7.1
unnamed: C5.2, L2.1, R7.2, U$3.21 (IOUTB)
unnamed: C11.1, U$4.23 (ICOMP)
unnamed: C9.2, L6.2, L8.1
unnamed: C12.1, U$3.23 (ICOMP)
OE_MEM: U$1.41 (~OE), U$2.41 (~OE); also elsewhere on the board
OE_SWITCH: IC8.25 (2G), IC8.48 (1G), IC9.25 (2G), IC9.48 (1G), IC15.2 (I1), R2.2, R3.1; also elsewhere on the board
QBN: C7.1, L3.2, R10.2; also elsewhere on the board
QBP: C7.2, L4.2, R10.1; also elsewhere on the board
VCC: C19.1, C20.1, IC8.1 (1DIR), IC8.7 (VCC@1), IC8.18 (VCC@2), IC8.24 (2DIR), IC8.31 (VCC@3), IC8.42 (VCC@4), IC9.1 (1DIR), IC9.7 (VCC@1), IC9.18 (VCC@2), IC9.24 (2DIR), IC9.31 (VCC@3), IC9.42 (VCC@4), IC15.5 (VCC), R2.1, R3.2, U$1.11 (3.3V), U$1.33 (3.3V), U$2.11 (3.3V), U$2.33 (3.3V), U$3.27 (DVDD), U$4.27 (DVDD); also elsewhere on the board
WE_I: U$2.17 (~WE); also elsewhere on the board
WE_Q: U$1.17 (~WE); also elsewhere on the board

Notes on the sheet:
Low Pass Filter <10 MHz
Amp Voltage State
Ensures high Z during startup
Use Metal Film for low noise.
